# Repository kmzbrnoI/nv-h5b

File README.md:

NV-H5B
======

NV-H5B is a [S-COM](https://www.mtb-model.com/elektro/s-com.htm) receiver based
on [NV-7B](https://www.mtb-model.com/elektro/s-com-nav.htm). It is mounted
to the socket of a signal and displays signal code according to the received code
on data wire.

This repository contains KiCad schematics & pcb layout design as well as MCU
firmware source code.

## Basic features

 * 5 V power supply.
 * Mechanical compatibility with [NV-7D](https://www.mtb-model.com/elektro/s-com-nav.htm).
 * Receives [standard S-COM protocol](https://www.mtb-model.com/elektro/s-com.htm).
 * Separate resistor for each LED to unify brightness.
 * ATtiny25 main MCU.
 * Opensource & openhardware design.
 * [Supported signals (CZ)](signals.md).

## Recommended resistor values

### AŽD 70 signals by Josef Němeček

* Yellow: 4k7
* Red: 10k
* White: 22k
* Green: 2k2
* Blue: 22k

### AŽD 65 signals by Mr. Dvořáček (Pečky)

* Yellow: 1k
* Red: 10k
* White: 22k
* Green: 1k
* Blue: 47k

## Authors

 * [Jan Horacek](mailto:jan.horacek@kmz-brno.cz)

## License

PCBs are provided under [Creative Commons Attribution-ShareAlike 4.0
License](https://creativecommons.org/licenses/by-sa/4.0/) as openhardware
project. You may download any data, contribute to the project, create PCB
yourself or even sell it yourself.

Source code is provided under the [Apache License v2.0
](https://www.apache.org/licenses/LICENSE-2.0).

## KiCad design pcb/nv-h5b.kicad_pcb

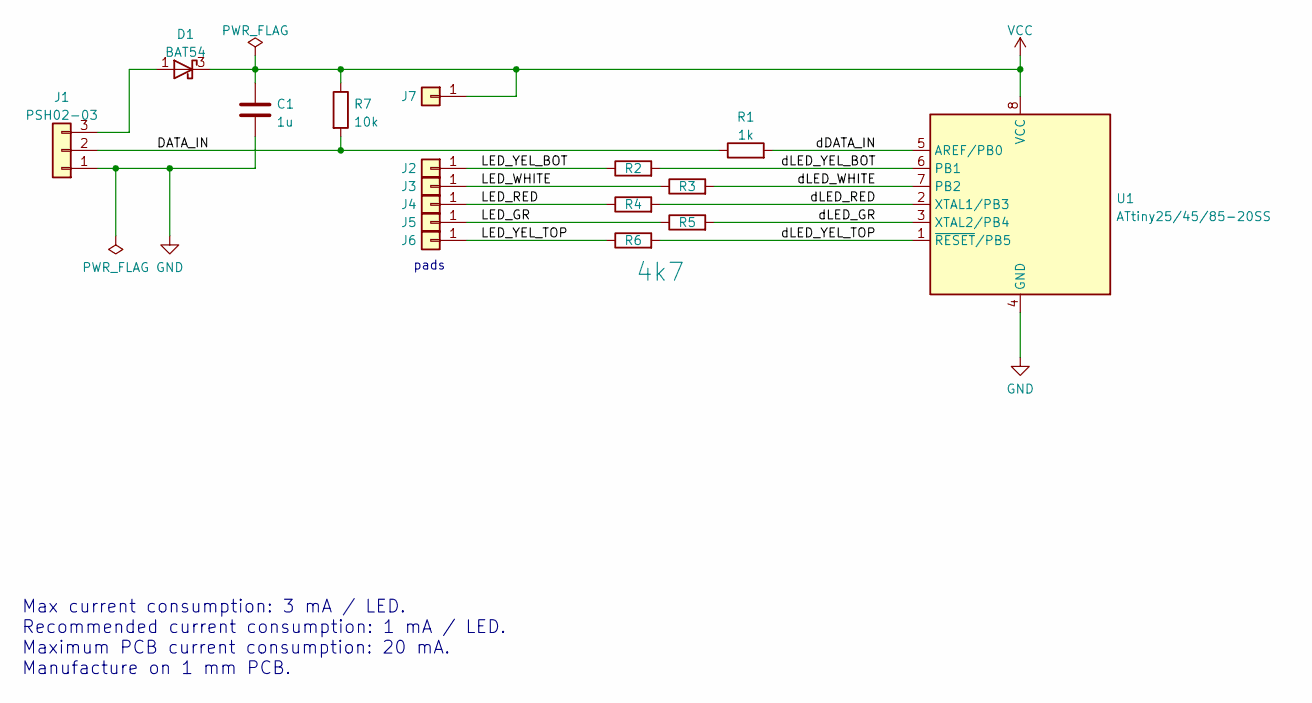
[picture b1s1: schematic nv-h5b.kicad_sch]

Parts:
C1: 1u; C_0805_2012Metric
D1: BAT54; SOT-23
J1: PSH02-03; PinHeader_1x03_P2.54mm_Horizontal
J2, J3, J4, J5, J6, J7: Conn_01x01; TestPoint_Keystone_5015_Micro-Minature
R1: 1k; R_0805_2012Metric
R2, R3, R4, R5, R6: 4k7; R_0805_2012Metric
R7: 10k; R_0805_2012Metric
U1: ATtiny25/45/85-20SS; SOIC-8_3.9x4.9mm_P1.27mm

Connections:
/DATA_IN: J1.2, R1.1, R7.2
/LED_GR: J5.1, R5.1
/LED_RED: J4.1, R4.1
/LED_WHITE: J3.1, R3.1
/LED_YEL_BOT: J2.1, R2.1
/LED_YEL_TOP: J6.1, R6.1
/dDATA_IN: R1.2, U1.5 (AREF/PB0)
/dLED_GR: R5.2, U1.3 (XTAL2/PB4)
/dLED_RED: R4.2, U1.2 (XTAL1/PB3)
/dLED_WHITE: R3.2, U1.7 (PB2)
/dLED_YEL_BOT: R2.2, U1.6 (PB1)
/dLED_YEL_TOP: R6.2, U1.1 (~RESET/PB5)
GND: C1.2, J1.1, U1.4 (GND)
unnamed: D1.1 (A), J1.3
VCC: C1.1, D1.3 (K), J7.1, R7.1, U1.8 (VCC)

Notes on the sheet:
Max current consumption: 3 mA / LED. Recommended current consumption: 1 mA / LED. Maximum PCB current consumption: 20 mA. Manufacture on 1 mm PCB.
pads

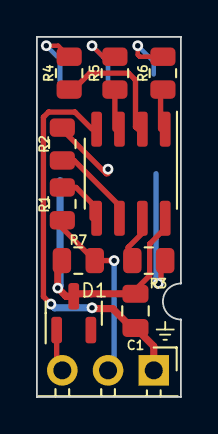
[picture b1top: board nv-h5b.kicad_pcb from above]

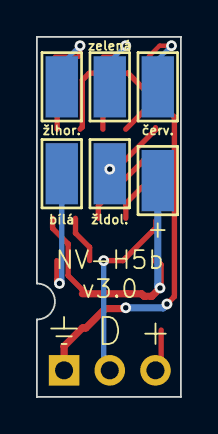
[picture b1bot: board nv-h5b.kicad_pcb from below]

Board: 2 copper layers, 8.0 x 20.0 mm, 17 parts (6 on the bottom side), 15 nets.

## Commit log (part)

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2020-08-15 Add .gitignore.
2020-08-15 Initial version of schematics & PCB.
2020-08-15 Increase main capacitor.
2020-08-15 Increase LED resistors (~ max. 3 mA/ LED).
2020-08-15 Add info about power consumption.
2020-08-15 Use vector font for silkscreen.
2020-08-15 Move pcb layout to separate repository.
2020-08-15 PCB: add version.
2020-08-15 Add basic README.
2020-08-15 Add firmware template.
2020-08-15 fw: add leds basic functions.
2020-08-15 Add pwm module.
2020-08-15 Add test LED setting.
2020-08-15 Setup timer 0 @ 1 kHz.
2020-08-15 Balance PWM & timer frequency.
2020-08-15 Make PWM for all LEDs work.
2020-08-15 Add signal codes.
2020-08-15 Pwm: use #define to spare RAM.
2020-08-15 Make signal code setting work.
2020-08-15 Make flashing codes work.
2020-08-16 Use global counter & save RAM.
    Spare stack space when calling update.
2020-08-17 Add code receiving & upgrade CPU.
2020-08-17 Add codes for second signal type.
2020-08-17 Add signal type detection (untested).
2020-08-17 sch: use ATtiny25.
2020-08-17 Fix really silly bug.
2020-08-17 Add initial signal code setting.
2020-08-17 Add proper fuses & F_CPU to Makefile.
2020-08-17 Make S-COM code decoding work.
2020-08-17 Add double-check for code receiving.
2020-08-17 Do not show out-of-range codes.
2020-08-17 Switch MSB & LSB when receiving signal.
2020-08-18 Fix 0 code receiving.
2020-08-18 Tune PWM parameters for smaller period.
2020-08-18 Tweak flashing based on real signals videos.
2020-08-18 Do not interfere ramps.
2020-08-18 Fix flash code changes.
2020-08-18 Fix empty signal code.
2020-08-18 Remap LED for real MCU.
2020-08-21 Set LED properly when PWM rewrite.
2020-08-21 Move code to avoid race condition due to interrupt.
2020-08-21 Fix signal turnoff.
2020-08-21 Add missing turnof for blinking & !flash_state.
2020-08-21 Enable watchdog.
2020-09-22 Opravit orientaci vstupniho konektoru.
    Bylo opacne GND & VCC.
2020-09-22 Fix S-COM codes 9 & 10, add code 16.
2020-10-09 Make side drill smaller.
2021-03-20 Fix watchdog initialization.
2023-03-05 Move 'pcb' to 'old' directory (new PCB in KiCad).
2023-03-05 Update Eagle version.
2023-03-05 Add empty KiCad project.
2023-03-05 Finalize schematics.
2023-03-05 Route PCB.
2023-03-05 Silkscreen.
2023-03-05 Add panelization Makefile.
2023-03-05 kikit panelize: add tolerance.
2023-03-09 Add part names to silkscreen.
2023-03-09 Add *.kicad_prl to .gitignore.
2023-03-09 Create tester PCB: copy from NV-H5B pcb.
2023-03-09 Tester: add LEDs to chematics, route PCB.
2023-03-12 Use thin top width.
    Because signal must fit in tracks profile.
2023-03-15 NV-H5B tester -> NV-H5T.
2023-03-15 Add 3V3 stabilizer, so NV-H5T supports both 5V & 12V power supply.
2023-03-15 Make panel.
2023-03-19 Do not write eeprom.
2023-03-19 Note possible alterantive versions of MCU.
2023-03-21 Add AZD 70 resistor values.
2023-12-07 Remove silkscreen of main connector outside of PCB.
2023-12-20 Makefile: add minipro flashing.
2023-12-20 Add fuses.conf.
2023-12-26 Simplify Makefile.
2023-12-26 Move .c & . to 'src' dir.
2023-12-26 Simplify .gitignore.
2023-12-26 README: add links, enhance texts.
2024-07-04 Do not write flashing output to first item in record.
2024-07-04 Delay turning the red LED off.
    In reality, the red light is turned off only after a successful validation
    of the allowing aspect.
2024-07-05 Always reset signal counter.
    Avoid the need for relationship with 65536.
2024-07-05 Save space by changing type to uint8_t.
2024-07-05 Use enum for signal type.
2024-07-05 Use void where appropriate.
2024-07-05 Add initial led test.
2024-07-06 Receive code during init test.
    If valid code is already received at the end of the initial test,
    show directly the code.
2024-07-07 Decrease red LED turnoff delay to 150 ms.
    This a more realisitc behavior.
    Previous value: ~800 ms.
2024-07-07 Place firmware name & version at the end of flash.
2024-07-20 README: add AZD 65 recommended resistor values.
2024-08-03 Use new fuses.conf format (minipro v0.7).
2024-08-03 README: update AZD 65 recommended resistors.
2024-08-06 Better S-COM variant detection.
2024-08-09 AZD65: add recommended blue resistor.
2024-12-04 README: add blue LED resistor value (22k).
2025-05-02 Prolong red-turnoff-delay to 550 ms.
    Recorded in real world: 630 ms.
2025-06-19 Add table of supported signals.
2025-06-19 Signals: full text, add first extension.
2025-06-19 signals.md: add more explanation.
2025-06-19 Add more new signals.
2025-06-19 Signals: add repeating signals for higher speeds.
2025-06-20 signal: add speed indicators.
2025-06-20 signals.md: add lights & expected codes.
2025-06-20 signals.md: add note regarding RIA & RIB general outputs.
2025-06-20 signals.md: add examples, add notes.
2025-06-21 signals.md: fix flicker frequency.
2025-06-22 signals.md: add open points.
2025-07-20 Disable spare peripherals to reduce power consumption.

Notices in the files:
pcb/nv-h5b.kicad_sch:
Released under the Creative Commons Attribution-ShareAlike 4.0 License
